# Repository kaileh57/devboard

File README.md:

# devboard

I've finally gotten BACK into PCB design!!

This project heavily expands on my previous work both in scope and complexity. 
It's an RP2040 devboard, which I hope to use for other projects. This was definetly outside of my comfort zone (I'm a software guy) but I got it done in the end after many many hours of routing traces :(
Looking forward to the next project, which is hopefully more complex!
It includes FOUR status LEDs, hooked up to GPIO pins 14-17
I also labeled each pin, as my past use of devboards in class has required a lot of referencing the design spec, which I hope to cut down here.

Schematic:

Design:

Render:

Feel free to use this devboard! It's MIT, but I'd appreciate at least a nod if you find it useful.

Made for Hack Club Blueprint: https://blueprint.hackclub.com/

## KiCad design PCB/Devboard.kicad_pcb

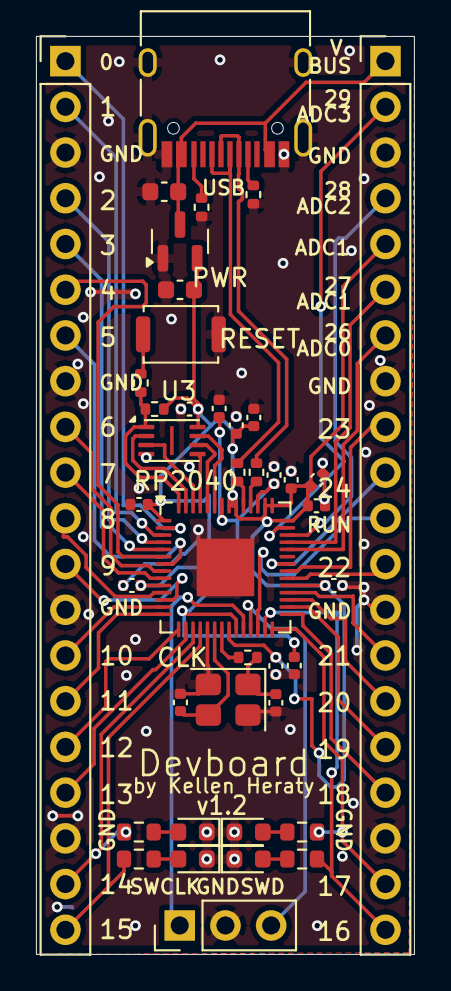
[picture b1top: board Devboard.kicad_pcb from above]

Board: 2 copper layers, 21.0 x 51.0 mm, 41 parts (0 on the bottom side), 56 nets.

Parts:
C1, C10: 1uF; C_0402_1005Metric
C2, C3, C4, C5, C6, C7, C8, C9, C11, C12, C17: 0.1uF; C_0402_1005Metric
C13, C14: 10uF; C_0603_1608Metric
C15, C16: 33pF; C_0402_1005Metric
CLK: 12 MHz; Crystal_SMD_3225-4Pin_3.2x2.5mm
D1, D2, D3, D4: LED; LED_0603_1608Metric
J2, J3: Conn_01x20; PinHeader_1x20_P2.54mm_Vertical
J4: Conn_01x03; PinHeader_1x03_P2.54mm_Vertical
PWR: MCP1700x-330xxTT; SOT-23
R1, R2: 5.1K; R_0402_1005Metric
R3, R4: 27; R_0402_1005Metric
R5, R6: 1k; R_0402_1005Metric
R7: 10k; R_0402_1005Metric
R8, R9, R10, R11: 330; R_0603_1608Metric
RESET: SW_Push; SW_Push_SPST_NO_Alps_SKRK
RP2040: RP2040; QFN-56-1EP_7x7mm_P0.4mm_EP3.2x3.2mm
U3: W25Q16JVSS; Winbond_USON-8-1EP_3x2mm_P0.5mm_EP0.2x1.6mm
USB: USB_C_Receptacle_USB2.0_14P; USB_C_Receptacle_HRO_TYPE-C-31-M-12

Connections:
+1V1: C10.1, C11.1, C12.1, RP2040.23 (DVDD), RP2040.45 (VREG_VOUT), RP2040.50 (DVDD)
+3V3: C1.1, C2.1, C3.1, C4.1, C5.1, C6.1, C7.1, C8.1, C9.1, C14.1, C17.1, J3.5, PWR.2 (VO), R7.1, RP2040.1 (IOVDD), RP2040.10 (IOVDD), RP2040.22 (IOVDD), RP2040.33 (IOVDD), RP2040.42 (IOVDD), RP2040.43 (ADC_AVDD), RP2040.44 (VREG_IN), RP2040.48 (USB_VDD), RP2040.49 (IOVDD), U3.8 (VCC)
GND: C1.2, C2.2, C3.2, C4.2, C5.2, C6.2, C7.2, C8.2, C9.2, C10.2, C11.2, C12.2, C13.2, C14.2, C15.1, C16.1, C17.2, CLK.2, CLK.4, D1.1 (K), D2.1 (K), D3.1 (K), D4.1 (K), J2.3, J2.8, J2.13, J2.18, J3.3, J3.8, J3.13, J3.18, J4.2, PWR.1 (GND), R1.2, R2.2, RESET.1, RP2040.19 (TESTEN), RP2040.57 (GND), U3.4 (GND), USB.A1 (GND), USB.A12 (GND), USB.B1 (GND), USB.B12 (GND), USB.S1 (SHIELD)
GPIO0: J2.1, RP2040.2 (GPIO0)
GPIO1: J2.2, RP2040.3 (GPIO1)
GPIO2: J2.4, RP2040.4 (GPIO2)
GPIO3: J2.5, RP2040.5 (GPIO3)
GPIO4: J2.6, RP2040.6 (GPIO4)
GPIO5: J2.7, RP2040.7 (GPIO5)
GPIO6: J2.9, RP2040.8 (GPIO6)
GPIO7: J2.10, RP2040.9 (GPIO7)
GPIO8: J2.11, RP2040.11 (GPIO8)
GPIO9: J2.12, RP2040.12 (GPIO9)
GPIO10: J2.14, RP2040.13 (GPIO10)
GPIO11: J2.15, RP2040.14 (GPIO11)
GPIO12: J2.16, RP2040.15 (GPIO12)
GPIO13: J2.17, RP2040.16 (GPIO13)
GPIO14: J2.19, R8.2, RP2040.17 (GPIO14)
GPIO15: J2.20, R9.2, RP2040.18 (GPIO15)
GPIO16: J3.20, R10.2, RP2040.27 (GPIO16)
GPIO17: J3.19, R11.2, RP2040.28 (GPIO17)
GPIO18: J3.17, RP2040.29 (GPIO18)
GPIO19: J3.16, RP2040.30 (GPIO19)
GPIO20: J3.15, RP2040.31 (GPIO20)
GPIO21: J3.14, RP2040.32 (GPIO21)
GPIO22: J3.12, RP2040.34 (GPIO22)
GPIO23: J3.9, RP2040.35 (GPIO23)
GPIO24: J3.10, RP2040.36 (GPIO24)
GPIO26_ADC0: J3.7, RP2040.38 (GPIO26_ADC0)
GPIO27_ADC1: J3.6, RP2040.39 (GPIO27_ADC1)
GPIO28_ADC2: J3.4, RP2040.40 (GPIO28_ADC2)
GPIO29_ADC3: J3.2, RP2040.41 (GPIO29_ADC3)
unnamed: C16.2, CLK.1, R5.1
unnamed: D1.2 (A), R8.1
unnamed: D2.2 (A), R9.1
unnamed: D3.2 (A), R10.1
unnamed: D4.2 (A), R11.1
unnamed: R2.1, USB.A5 (CC1)
unnamed: R1.1, USB.B5 (CC2)
unnamed: R6.2, RESET.2
unnamed: R4.1, RP2040.46 (USB_DM)
unnamed: R3.1, RP2040.47 (USB_DP)
QSPI_SCLK: RP2040.52 (QSPI_SCLK), U3.6 (CLK)
QSPI_SD0: RP2040.53 (QSPI_SD0), U3.5 (DI/IO_{0})
QSPI_SD1: RP2040.55 (QSPI_SD1), U3.2 (DO/IO_{1})
QSPI_SD2: RP2040.54 (QSPI_SD2), U3.3 (~WP/IO_{2})
QSPI_SD3: RP2040.51 (QSPI_SD3), U3.7 (~HOLD/~RESET/IO_{3})
QSPI_SS: R6.1, R7.2, RP2040.56 (QSPI_SS), U3.1 (~CS)
RUN: J3.11, RP2040.26 (RUN)
SWCLK: J4.1, RP2040.24 (SWCLK)
SWD: J4.3, RP2040.25 (SWD)
USB_D+: R3.2, USB.A6 (D+), USB.B6 (D+)
USB_D-: R4.2, USB.A7 (D-), USB.B7 (D-)
VBUS: C13.1, J3.1, PWR.3 (VI), USB.A4 (VBUS), USB.A9 (VBUS), USB.B4 (VBUS), USB.B9 (VBUS)
XIN: C15.2, CLK.3, RP2040.20 (XIN)
XOUT: R5.2, RP2040.21 (XOUT)

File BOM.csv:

JLCPCB BOM Tool - BOM Matching,,,,,,,,,,,,,,,,,
BOM name：Devboard-JLCPCB Assembly Order.xlsx,,,Download Time：2025-12-09 14:25:52,,,,"* Our matching results are updated in real-time, but stock and prices may change. 
If it's been over 24 hours, please re-match before placing your order.",,,,,,,,,,
PCB Assembled Qty：5,,,Est. Total Price：5.6637,,,,,,,,,,,,,,
Your BOM,,,,,Matched Parts,,,,,,,Order Information,,,,,
Top Designator,Bottom Designator,Comment,Footprint,JLCPCB Part #,Matches,Part # ,Manufacturer,Footprint,Description,Category,Warning,JLCPCB Part #,Product link,Lib Type,Qty,Source,Total Price ($)
"C2,C5,C17,C4,C6,C7,C11,C12,C3,C9,C8",,0.1uF,C_0402_1005Metric,,Select by Customer,CL05B104KO5NNNC,Samsung Electro-Mechanics,0402,100nF 16V X7R ±10% 0402 Multilayer Ceramic Capacitors MLCC - SMD/SMT ROHS,Multilayer Ceramic Capacitors MLCC - SMD/SMT,1.The comment (CL05B104KO5NNNC) of this part does not match the one (0.1uF) provided in your BOM. Please confirm;,C1525,https://jlcpcb.com/partdetail/1877-CL05B104KO5NNNC/C1525,Basic,22,22 JLCPCB,0.0264
"C10,C1",,1uF,C_0402_1005Metric,,Select by Customer,CL05A105KA5NQNC,Samsung Electro-Mechanics,0402,1uF 25V X5R ±10% 0402 Multilayer Ceramic Capacitors MLCC - SMD/SMT ROHS,Multilayer Ceramic Capacitors MLCC - SMD/SMT,,C52923,https://jlcpcb.com/partdetail/53938-CL05A105KA5NQNC/C52923,Basic,4,4 JLCPCB,0.0116
"C14,C13",,10uF,C_0603_1608Metric,,Select by Customer,CL10A106KP8NNNC,Samsung Electro-Mechanics,0603,10V 10uF X5R ±10% 0603 Multilayer Ceramic Capacitors MLCC - SMD/SMT ROHS,Multilayer Ceramic Capacitors MLCC - SMD/SMT,,C19702,https://jlcpcb.com/partdetail/20411-CL10A106KP8NNNC/C19702,Basic,4,4 JLCPCB,0.0224
"C15,C16",,33pF,C_0402_1005Metric,,Select by Customer,0402CG330J500NT,FH (Guangdong Fenghua Advanced Tech),0402,33pF 50V C0G ±5% 0402 Multilayer Ceramic Capacitors MLCC - SMD/SMT ROHS,Multilayer Ceramic Capacitors MLCC - SMD/SMT,,C1562,https://jlcpcb.com/partdetail/1914-0402CG330J500NT/C1562,Basic,4,4 JLCPCB,0.004
CLK,,12MHz,Crystal_SMD_3225-4Pin_3.2x2.5mm,,Select by Customer,X322512MSB4SI,YXC Crystal Oscillators,SMD3225-4P,-40℃~+85℃ 12MHz 20pF Crystal Oscillator ±10ppm ±20ppm SMD3225-4P Crystals ROHS,Crystals,,C9002,https://jlcpcb.com/partdetail/YXC_CrystalOscillators-X322512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,Basic,2,2 JLCPCB,0.129
"D4,D3,D2,D1",,LED,LED_0603_1608Metric,,Select by Customer,KT-0603R,Hubei KENTO Elec,0603,-40℃~+85℃ 120° 2.4V 20mA 300mcd 40mW 615nm~630nm 645nm Red Water Clear 0603 LED Indication - Discrete ROHS,LED Indication - Discrete,1.The comment (KT-0603R) of this part does not match the one (LED) provided in your BOM. Please confirm;,C2286,https://jlcpcb.com/partdetail/Hubei_KENTOElec-KT0603R/C2286,Basic,8,8 JLCPCB,0.0448
"J3,J2",,Conn_01x20,PinHeader_1x20_P2.54mm_Vertical,,Select by Customer,2.54-1*20P直针,BOOMELE(Boom Precision Elec),"插件,P=2.54mm","-40℃~+105℃ 1 1x20P 2.54mm 20P 3A Black Brass Pin Header Through Hole Plugin,P=2.54mm Pin Headers ROHS",Pin Headers,,C50981,https://jlcpcb.com/partdetail/51993-2_54_1_20P/C50981,Extended,0,0 JLCPCB,0
J4,,Conn_01x03,PinHeader_1x03_P2.54mm_Vertical,,Select by Customer,1.27-1*3P针,BOOMELE(Boom Precision Elec),"插件,P=1.27mm","-55℃~+105℃ 1 1.27mm 1mm 1x3P 2.3mm 3A 3P 3mm Black Brass Pin Header Through Hole Plugin,P=1.27mm Pin Headers ROHS",Pin Headers,,C24980,https://jlcpcb.com/partdetail/25717-1_27_1_3P/C24980,Extended,0,0 JLCPCB,0
PWR,,MCP1700x-330xxTT,SOT-23,,Select by Customer,MCP1700T-3302E/TT,Microchip Tech,SOT-23,"-40℃~+125℃@(Tj) 1 1.6uA 178mV@(250mA) 250mA 3.3V 44dB@(100Hz) 6V Fixed Over Temperature Protection Positive SOT-23 Voltage Regulators - Linear, Low Drop Out (LDO) Regulators ROHS","Voltage Regulators - Linear, Low Drop Out (LDO) Regulators",,C39051,https://jlcpcb.com/partdetail/MicrochipTech-MCP1700T_3302ETT/C39051,Extended,5,5 JLCPCB,1.9695
"R1,R2",,5.1K,R_0402_1005Metric,,Select by Customer,0402WGF5101TCE,UNI-ROYAL(Uniroyal Elec),0402,-55℃~+155℃ 5.1kΩ 50V 62.5mW Thick Film Resistor ±1% ±100ppm/℃ 0402 Chip Resistor - Surface Mount ROHS,Chip Resistor - Surface Mount,,C25905,https://jlcpcb.com/partdetail/26648-0402WGF5101TCE/C25905,Basic,4,4 JLCPCB,0.002
"R4,R3",,27,R_0402_1005Metric,,Select by Customer,0402WGF270JTCE,UNI-ROYAL(Uniroyal Elec),0402,-55℃~+155℃ 27Ω 50V 62.5mW Thick Film Resistor ±1% ±100ppm/℃ 0402 Chip Resistor - Surface Mount ROHS,Chip Resistor - Surface Mount,1.The comment (0402WGF270JTCE) of this part does not match the one (27) provided in your BOM. Please confirm;,C25100,https://jlcpcb.com/partdetail/25843-0402WGF270JTCE/C25100,Extended,20,20 JLCPCB,0.012
"R6,R5",,1k,R_0402_1005Metric,,Select by Customer,0402WGF1001TCE,UNI-ROYAL(Uniroyal Elec),0402,-55℃~+155℃ 1kΩ 50V 62.5mW Thick Film Resistor ±1% ±100ppm/℃ 0402 Chip Resistor - Surface Mount ROHS,Chip Resistor - Surface Mount,1.The comment (0402WGF1001TCE) of this part does not match the one (1k) provided in your BOM. Please confirm;,C11702,https://jlcpcb.com/partdetail/12256-0402WGF1001TCE/C11702,Basic,4,4 JLCPCB,0.0024
R7,,10k,R_0402_1005Metric,,Select by Customer,0402WGF1002TCE,UNI-ROYAL(Uniroyal Elec),0402,-55℃~+155℃ 10kΩ 50V 62.5mW Thick Film Resistor ±1% ±100ppm/℃ 0402 Chip Resistor - Surface Mount ROHS,Chip Resistor - Surface Mount,1.The comment (0402WGF1002TCE) of this part does not match the one (10k) provided in your BOM. Please confirm;,C25744,https://jlcpcb.com/partdetail/26487-0402WGF1002TCE/C25744,Basic,2,2 JLCPCB,0.001
"R11,R10,R9,R8",,330,R_0603_1608Metric,,Select by Customer,0603WAF3300T5E,UNI-ROYAL(Uniroyal Elec),0603,-55℃~+155℃ 100mW 330Ω 75V Thick Film Resistor ±1% ±100ppm/℃ 0603 Chip Resistor - Surface Mount ROHS,Chip Resistor - Surface Mount,1.The comment (0603WAF3300T5E) of this part does not match the one (330) provided in your BOM. Please confirm;,C23138,https://jlcpcb.com/partdetail/23865-0603WAF3300T5E/C23138,Basic,8,8 JLCPCB,0.0088
RESET,,SW_Push,SW_Push_SPST_NO_Alps_SKRK,,Select by Customer,TS-1088-AR02016,XUNPU,"SMD,4x3mm","-30℃~+80℃ 1.6N 100,000 Cycles 12V 2mm 3mm 4mm 50mA Black Round Button SMD(SMT) Tab SPST Surface Mount,Vertical Without Bracket SMD,4x3mm Tactile Switches ROHS",Tactile Switches,,C720477,https://jlcpcb.com/partdetail/XUNPU-TS_1088AR02016/C720477,Basic,2,2 JLCPCB,0.085
RP2040,,RP2040,QFN-56-1EP_7x7mm_P0.4mm_EP3.2x3.2mm,,Select by Customer,RP2040,Raspberry Pi,LQFN-56(7x7),12bit 133MHz 30 LQFN-56(7x7) Microcontrollers (MCU/MPU/SOC) ROHS,Microcontrollers (MCU/MPU/SOC),,C2040,https://jlcpcb.com/partdetail/RaspberryPi-RP2040/C2040,Extended,2,2 JLCPCB,1.833
U3,,W25Q16JVSS,Winbond_USON-8-1EP_3x2mm_P0.5mm_EP0.2x1.6mm,,Select by Customer,W25Q16JVUXIQ,Winbond Elec,USON-8-EP(2x3),"-40℃~+85℃ 100,000 Cycles 10uA 133MHz 16Mbit 2.7V~3.6V 20 Years 3ms SPI USON-8-EP(2x3) NOR FLASH ROHS",NOR FLASH,1.The comment (W25Q16JVUXIQ) of this part does not match the one (W25Q16JVSS) provided in your BOM. Please confirm;,C2843335,https://jlcpcb.com/partdetail/WinbondElec-W25Q16JVUXIQ/C2843335,Extended,2,2 JLCPCB,1.173
USB,,USB_C_Receptacle_USB2.0_14P,USB_C_Receptacle_HRO_TYPE-C-31-M-12,,Select by Customer,TYPE-C-31-M-12,Korean Hroparts Elec,SMD,1 16P 5A Female Type-C SMD USB Connectors ROHS,USB Connectors,,C165948,https://jlcpcb.com/partdetail/Korean_HropartsElec-TYPE_C_31_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,Extended,2,2 JLCPCB,0.3388

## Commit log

2025-11-29 setup
2025-11-29 Enhance README with project details and images
    Expanded the README with details about the RP2040 devboard project, including personal insights and design images.
2025-11-29 Add MIT License to the project
2025-11-29 Add journal entries for PCB project progress
    Documented the progress and updates on the PCB project, including schematic layout, footprint application, routing, and final adjustments.
2025-11-30 Add schematic image to README
    Added schematic image to the README for reference.
2025-12-09 added LEDs
2025-12-09 Add 4 LEDs for status indication and data flow
    Added 4 LEDs to the project for enhanced functionality, connected to GPIO pins 14-17, allowing for blinking or programmable status indication.
